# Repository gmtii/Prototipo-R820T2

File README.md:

Proyecto 'breakout' de un R820T2 más un QSD para obtener salida IQ directamente a la tarjeta de sonido del PC. La idea es experimentar con el R820T2 y un QSD cuya frecuencia de refencia es 4X a la de demodulación, generada por un Si5351. 

El proyecto contiene:

- Carpeta KICAD: esquemas y PCB directos para generar gerbers.

- Carpeta r820t2: código Arduino para controla el R820T2 y Si5351.

+ Existe un modo consola de comandos serial para controlar los registros del R820T2 directamente y experiemntar.

+ Modo CAT para controlar la frecuencia de sintonía a través de OMNIRIG y el HDSDR por ejemplo.

Los principales aspectos del diseño son:

- El microcontrolador que usemos debe ser 3.3V. 
- El código inicia el R820T2 mediante protocolo I2C. El led, pin 13, y la salida por el puerto serie nos dan indicación del proceso de inicio.
- La parte LOOP consiste en una librería CAT para controlar la frecuencia de sintonía mediante el PC, como por ejemplo el OMNIRIG y el HDSDR.

El principio de hardware es:

- La salida del R820T2 se fija en 5 MHz. El tuner hace un proceso de mezcla de la entrada RF, y la frecuencia de sintonía aparecerá en su salida en esos 5 MHz.
- Se emplea la salida CLKOUT del R820T2, como entrada para un Si5351. Lo ideal es usar un cristal de 25 Mhz en el R820T2.
- Se programa la salida del Si5351 CLK2 a 20 Mhz, que será la entrada del demodulador QSD. Esto realmente es un 'exceso' pero la idea es experimentar con el Si5351 también. Bastaría con instalar un TCXO de 20Mhz al R820T2 para tener exactamente la frecuencia necesaria de demodulación en el QSD, esto es 5 Mhz. Este TCXO sería precisamente el U1. 
- La conversión tiene lugar justo en esos 20MHz/4, esto es, 5 Mhz, justo la salida del R820T2.
- La salida IQ es pues en banda base y directamente aplicable a la tarjeta de sonido del PC. Es recomendable ajustar la entrada a 192 Khz para poder demodular WFM correctamente.
- Con cualquier software que soporte la tarjeta de sonido como entrada, SDR#, o HDSDR, por ejemplo, nos permitirá ver el espectro y demodular la señal resultante.

Modelo 3D de la placa PCB mediante KICAD:

El proyecto está basado en fuentes como:

Driver del kernel linux del R820T2 ofrecido bajo licencia GPL.
Datasheet del R820T2.
Breakout y fuentes del proyecto del R820T2 de Eric Brombaugh https://github.com/emeb/r820t2/. Licencia MIT.

Esteban EA8DGL estebanjbs < at > gmail.com

Breakout project of an R820T2 plus a QSD to get IQ output directly to the PC sound card. The idea is to experiment with the R820T2 and a QSD whose reference frequency is 4X that of demodulation, generated by a Si5351.

The project contains:

- KICAD folder: diagrams and direct PCBs to generate gerbers.

- r820t2 folder: Arduino code to control the R820T2 and Si5351.

+ There is a serial command console mode to control the registers of the R820T2 directly and experiment.

+ CAT mode to control the tuning frequency through OMNIRIG and HDSDR for example.

The main aspects of the design are:

- The microcontroller that we use must be 3.3V.
- The code starts the R820T2 using the I2C protocol. The led, pin 13, and the output through the serial port give us an indication of the startup process.
- The LOOP part consists of a CAT library to control the tuning frequency through the PC, such as OMNIRIG and HDSDR.

The hardware principle is:

- The R820T2's output is fixed at 5 MHz. The tuner does a process of mixing the RF input, and the tuning frequency will appear at its output at those 5 MHz.
- The CLKOUT output of the R820T2 is used as input for a Si5351. Ideally, use a 25Mhz crystal on the R820T2.
- The output of Si5351 CLK2 is programmed at 20 Mhz, which will be the input of the QSD demodulator. This really is 'overkill' but the idea is to experiment with the Si5351 as well. It would be enough to install a 20Mhz TCXO to the R820T2 to have exactly the necessary demodulation frequency in the QSD, this is 5 Mhz. This TCXO would be precisely U1.
- The conversion takes place right at those 20MHz / 4, that is, 5Mhz, just the output of the R820T2.
- The IQ output is thus in baseband and directly applicable to the PC sound card. It is recommended to set the input to 192 Khz in order to demodulate WFM correctly.
- With any software that supports the sound card as input, SDR #, or HDSDR, for example, it will allow us to see the spectrum and demodulate the resulting signal.

3D model of the PCB board using KICAD:

! [pcb] (pcb.PNG)

The project is based on sources such as:

R820T2 Linux kernel driver offered under the GPL license.
Datasheet of the R820T2.
Breakout and sources for Eric Brombaugh's R820T2 project https://github.com/emeb/r820t2/. MIT license.

Esteban EA8DGL estebanjbs <at> gmail.com

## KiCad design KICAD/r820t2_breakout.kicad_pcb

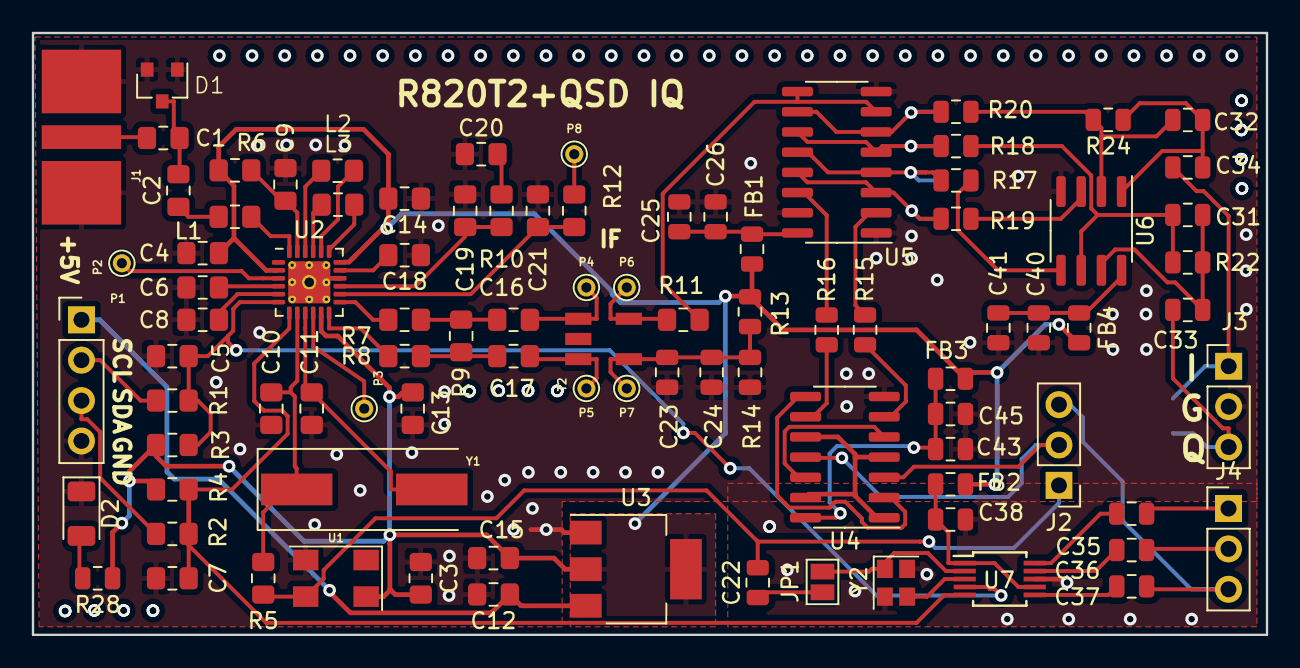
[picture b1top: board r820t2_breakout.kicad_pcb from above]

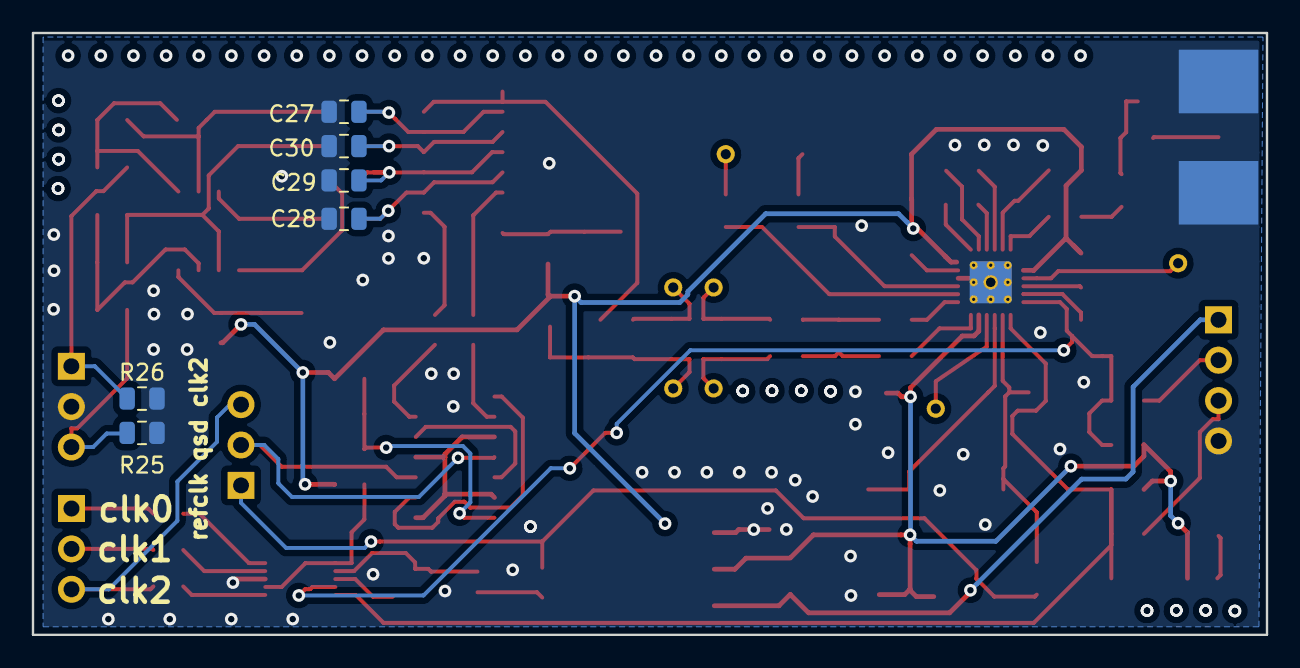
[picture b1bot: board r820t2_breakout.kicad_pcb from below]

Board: 2 copper layers, 77.6 x 37.8 mm, 99 parts (6 on the bottom side), 71 nets.

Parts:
C1: 0.01uf; C_0805_2012Metric_Pad1.15x1.40mm_HandSolder
C2, C19: 330pf; C_0805_2012Metric_Pad1.15x1.40mm_HandSolder
C3, C4, C8, C9, C13, C14, C16, C17, C18, C21: 0.1uf; C_0805_2012Metric_Pad1.15x1.40mm_HandSolder
C5, C7, C10, C11: 27pf; C_0805_2012Metric_Pad1.15x1.40mm_HandSolder
C6: 1uf; C_0805_2012Metric_Pad1.15x1.40mm_HandSolder
C12, C15: 10uf; C_0805_2012Metric_Pad1.15x1.40mm_HandSolder
C20: 6800pf; C_0805_2012Metric_Pad1.15x1.40mm_HandSolder
C22, C23, C25, C35, C36, C37, C38, C40, C43: 100nF; C_0805_2012Metric
C24, C26, C41, C45: 4.7uF; C_0805_2012Metric
C27, C28, C29, C30: 33nF; C_0805_2012Metric
C31, C32: 330p; C_0805_2012Metric
C33, C34: 2.2uF; C_0805_2012Metric
D1: BAV99; SOT-23
D2: LED; D_1206_3216Metric
FB1, FB2, FB3, FB4: Ferrite_Bead; L_0805_2012Metric
J1: SMA; SMA_END
J2, J4: CLK Source; PinHeader_1x03_P2.54mm_Vertical
J3: Conn_01x03_Male; PinHeader_1x03_P2.54mm_Vertical
JP1: SolderJumper_2_Open; SolderJumper-2_P1.3mm_Open_Pad1.0x1.5mm
L1: 8.2nH; R_0805_2012Metric_Pad1.15x1.40mm_HandSolder
L2, L3: 150nh; R_0805_2012Metric_Pad1.15x1.40mm_HandSolder
P1: CONN_01X04; Pin_Header_Straight_1x04_Pitch2.54mm
P2, P3, P4, P5, P6, P7, P8: CONN_01X01; PINTST
R1, R2, R7, R8: 220; R_0805_2012Metric_Pad1.15x1.40mm_HandSolder
R3, R4: 4k7; R_0805_2012Metric_Pad1.15x1.40mm_HandSolder
R5, R11: 0; R_0805_2012Metric_Pad1.15x1.40mm_HandSolder
R6: 10; R_0805_2012Metric_Pad1.15x1.40mm_HandSolder
R9: DNI; R_0805_2012Metric_Pad1.15x1.40mm_HandSolder
R10: 1k8; R_0805_2012Metric_Pad1.15x1.40mm_HandSolder
R12: 10k; R_0805_2012Metric_Pad1.15x1.40mm_HandSolder
R13, R14: 5.6k; R_0805_2012Metric
R15, R16: 0; R_0805_2012Metric
R17, R18, R19, R20: 100; R_0805_2012Metric
R22, R25, R26: 10k; R_0805_2012Metric
R24: 8.2k; R_0805_2012Metric
R28: 512; R_0805_2012Metric
T2: TRANSFO4; Pulse_SMD_Balun
U1: TWEAALSANF-28.800000; Crystal_SMD_Abracon_ABM3C-4pin_5.0x3.2mm
U2: R820T2; QFN-24-1EP_4x4mm_P0.5mm_EP2.65x2.65mm_ThermalVias
U3: LD1117S33CTR; SOT-223
U4: 74HC74; SOIC-14_3.9x8.7mm_P1.27mm
U5: SN74CBT3253; SOIC-16_3.9x9.9mm_P1.27mm
U6: LT6234; SOIC-8_3.9x4.9mm_P1.27mm
U7: Si5351A-B-GT; MSOP-10_3x3mm_P0.5mm
Y1: 20MHz; Crystal_SMD_HC49-SD
Y2: Crystal_GND24; Crystal_SMD_2520-4Pin_2.5x2.0mm

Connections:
+3.3V: U4.1, U4.4, U4.10, U4.13
+3V3: C3.2, C4.2, C13.2, C14.2, C15.1, FB1.1, FB2.1, FB3.1, FB4.1, R3.1, R4.1, R6.1, R13.2, R28.1, U1.4, U2.2, U2.11, U2.18, U3.2, U3.4
+5V: C12.1, P1.1, U3.3
CLK0: C35.1, J4.1
CLK1: C36.1, J4.2
CLK2: C37.1, J2.3, J4.3
GND: C3.1, C4.1, C5.1, C6.1, C7.1, C8.1, C9.1, C10.1, C11.1, C12.2, C13.1, C14.1, C15.2, C18.1, C19.1, C20.1, C21.1, C23.2, C24.2, C25.2, C26.2, C27.2, C28.2, C29.1, C30.2, C38.2, C40.2, C41.2, C43.2, C45.2, D1.1, D1.2, D2.1, J1.2, J3.2, P1.4, R14.1, R25.2, R26.2, U1.2, U2.16, U2.25, U3.1, U4.7, U5.1, U5.8, U5.15, U6.4, U7.8, Y2.2, Y2.4
IF_N: C23.1, C24.1, P7.1, R13.1, R14.2, T2.4
IF_P: R11.1, U5.7, U5.9
I_CLK: R16.1, U5.14
unnamed: C1.1, C2.2, D1.3
unnamed: C1.2, J1.1
unnamed: C2.1, L1.1
unnamed: C6.2, U2.4
unnamed: C8.2, U2.5
unnamed: C9.2, R6.2, U2.23
unnamed: C10.2, R5.1, U2.8, Y1.1
unnamed: C11.2, U2.9, Y1.2
unnamed: C16.1, P4.1, T2.1
unnamed: C16.2, R7.1, R9.1
unnamed: C17.1, P5.1, T2.3
unnamed: C17.2, R8.1, R9.2
unnamed: C18.2, U2.17
unnamed: C19.2, R10.2, U2.15
unnamed: C20.2, R10.1
unnamed: C21.2, R12.2, U2.14
unnamed: C22.1, JP1.1
unnamed: C25.1, C26.1, FB1.2, U5.16
unnamed: C27.1, R20.2, U5.6, U5.10
unnamed: C28.1, R19.2, U5.3, U5.13
unnamed: C29.2, R17.2, U5.4, U5.12
unnamed: C30.1, R18.2, U5.5, U5.11
unnamed: C31.1, C33.2, R22.1, U6.7
unnamed: C31.2, R18.1, R22.2, U6.6
unnamed: C32.1, C34.2, R24.1, U6.1
unnamed: C32.2, R20.1, R24.2, U6.2
unnamed: C35.2, U7.10
unnamed: C36.2, U7.9
unnamed: C37.2, U7.6
unnamed: C38.1, FB2.2, U7.1, U7.7
unnamed: C40.1, C41.1, FB4.2, U6.8
unnamed: C43.1, C45.1, FB3.2, U4.14
unnamed: D2.2, R28.2
unnamed: J2.2, U4.3, U4.11
unnamed: JP1.2, U7.2, Y2.1
unnamed: L1.2, U2.24
unnamed: L2.1, U2.20
unnamed: L2.2, U2.22
unnamed: L3.1, U2.19
unnamed: L3.2, U2.21
unnamed: P1.2, R1.2
unnamed: P1.3, R2.2
unnamed: P2.1, U2.3
unnamed: P3.1, U2.10
unnamed: P6.1, R11.2, T2.5
unnamed: P8.1, R12.1
unnamed: R7.2, U2.13
unnamed: R8.2, U2.12
unnamed: R15.2, U4.6
unnamed: R16.2, U4.9
unnamed: R17.1, U6.5
unnamed: R19.1, U6.3
unnamed: U4.5, U4.12
unnamed: U7.3, Y2.3
PHASE_I: C34.1, J3.1, R26.1
PHASE_Q: C33.1, J3.3, R25.1
Q_CLK: R15.1, U5.2
REFCLK: C22.2, J2.1, R5.2, U1.3
SCL: C5.2, R1.1, R3.2, U2.6, U7.4
SDA: C7.2, R2.1, R4.2, U2.7, U7.5
TXOUT: U4.2, U4.8
